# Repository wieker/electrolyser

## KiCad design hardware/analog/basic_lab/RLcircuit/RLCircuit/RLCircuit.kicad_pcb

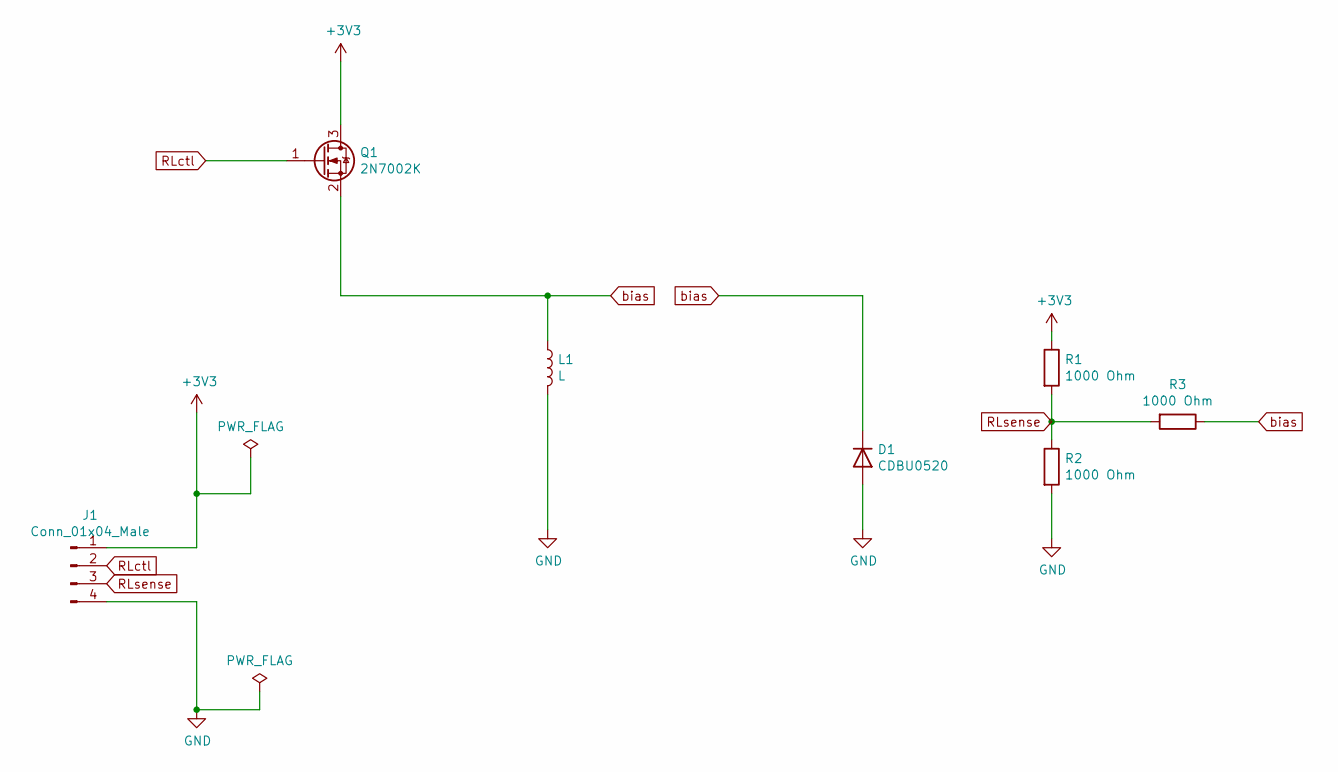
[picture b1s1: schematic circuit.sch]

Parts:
D1: CDBU0520; D_0603_1608Metric
J1: Conn_01x04_Male; PinHeader_1x04_P2.54mm_Vertical
L1: L; L_Axial_L12.0mm_D5.0mm_P5.08mm_Vertical_Fastron_MISC
Q1: 2N7002K; SOT-23
R1, R2, R3: 1000 Ohm; R_0402_1005Metric

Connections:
+3V3: J1.1, Q1.3 (D), R1.1
GND: D1.2 (A), J1.4, L1.2, R2.2
RLctl: J1.2, Q1.1 (G)
RLsense: J1.3, R1.2, R2.1, R3.2
bias: D1.1 (K), L1.1, Q1.2 (S), R3.1

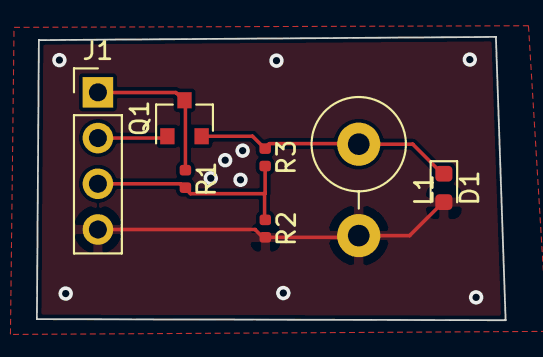
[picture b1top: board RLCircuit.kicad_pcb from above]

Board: 2 copper layers, 26.0 x 15.7 mm, 7 parts (0 on the bottom side), 5 nets.

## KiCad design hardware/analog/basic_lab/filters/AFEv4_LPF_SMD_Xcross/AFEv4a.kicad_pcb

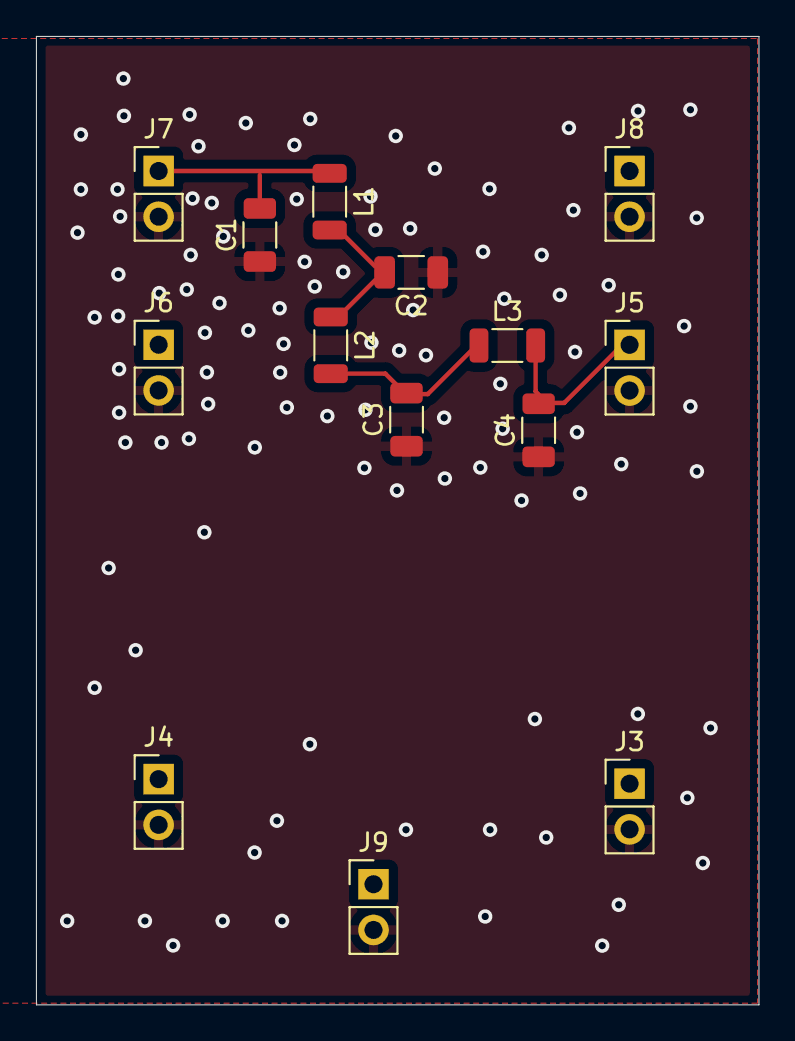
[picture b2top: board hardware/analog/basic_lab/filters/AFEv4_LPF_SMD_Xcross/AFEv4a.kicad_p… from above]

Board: 2 copper layers, 40.1 x 53.8 mm, 14 parts (0 on the bottom side), 5 nets.

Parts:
C1, C2, C3, C4: C; C_1206_3216Metric
J3, J4, J5, J6, J7, J8, J9: Connector_Generic_Conn_01x02; PinHeader_1x02_P2.54mm_Vertical
L1, L2, L3: L; L_1206_3216Metric

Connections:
GND: C1.1, C2.1, C3.1, C4.1, J3.2, J4.2, J5.2, J6.2, J7.2, J8.2, J9.2
unnamed: C2.2, L1.2, L2.1
unnamed: C3.2, L2.2, L3.1
bpf_ant: C4.2, J5.1, L3.2
bpf_lvds: C1.2, J7.1, L1.1

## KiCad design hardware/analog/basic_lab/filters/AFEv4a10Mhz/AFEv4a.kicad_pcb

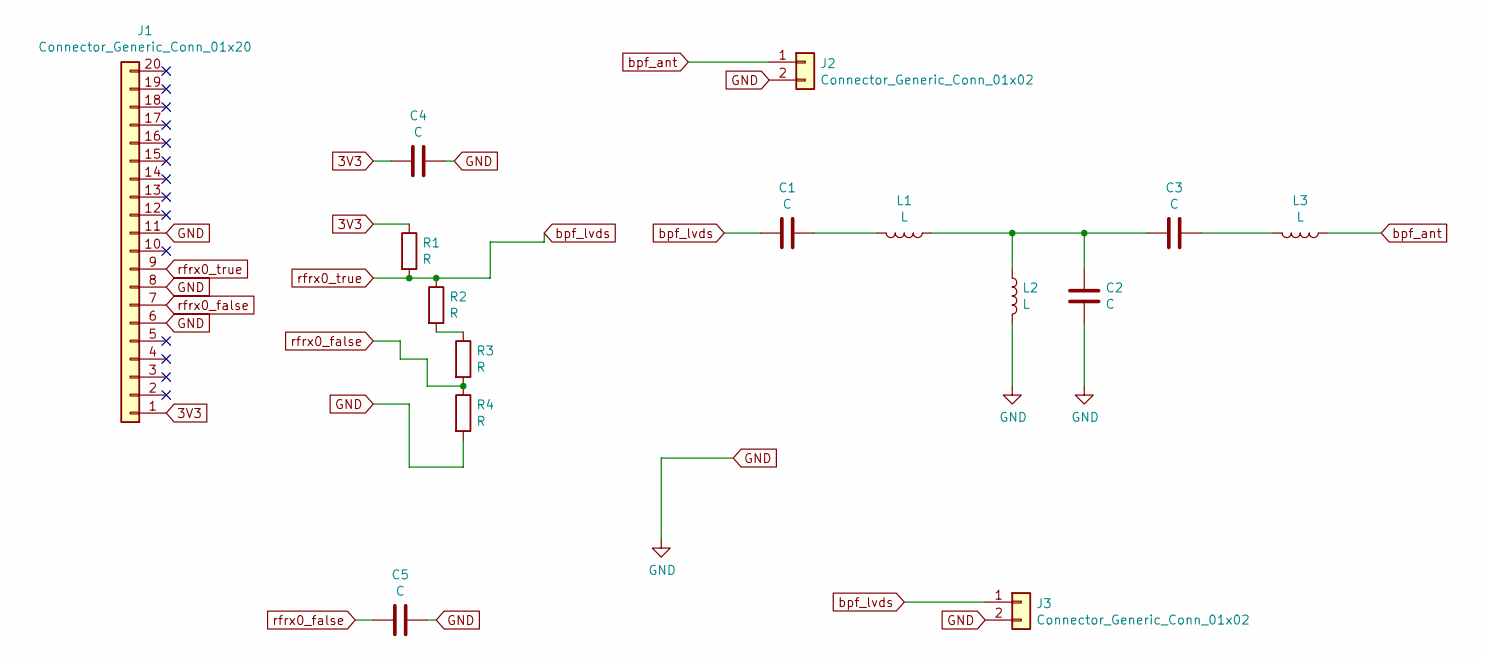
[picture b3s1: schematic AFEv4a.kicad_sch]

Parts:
C1, C2, C3: C; C_1206_3216Metric
C4, C5: C; C_Axial_L5.1mm_D3.1mm_P15.00mm_Horizontal
J1: Connector_Generic_Conn_01x20; PinHeader_1x20_P2.54mm_Vertical
J2, J3: Connector_Generic_Conn_01x02; PinHeader_1x02_P2.54mm_Vertical
L1, L2, L3: L; L_1206_3216Metric
R1, R2, R3, R4: R; R_Axial_DIN0207_L6.3mm_D2.5mm_P5.08mm_Vertical

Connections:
3V3: C4.2, J1.1, R1.1
GND: C2.2, C4.1, C5.1, J1.6, J1.8, J1.11, J2.2, J3.2, L2.2, R4.2
unnamed: C1.1, L1.2
unnamed: C2.1, C3.2, L1.1, L2.1
unnamed: C3.1, L3.2
unnamed: R2.2, R3.1
bpf_ant: J2.1, L3.1
bpf_lvds: C1.2, J1.9, J3.1, R1.2, R2.1
rfrx0_false: C5.2, J1.7, R3.2, R4.1

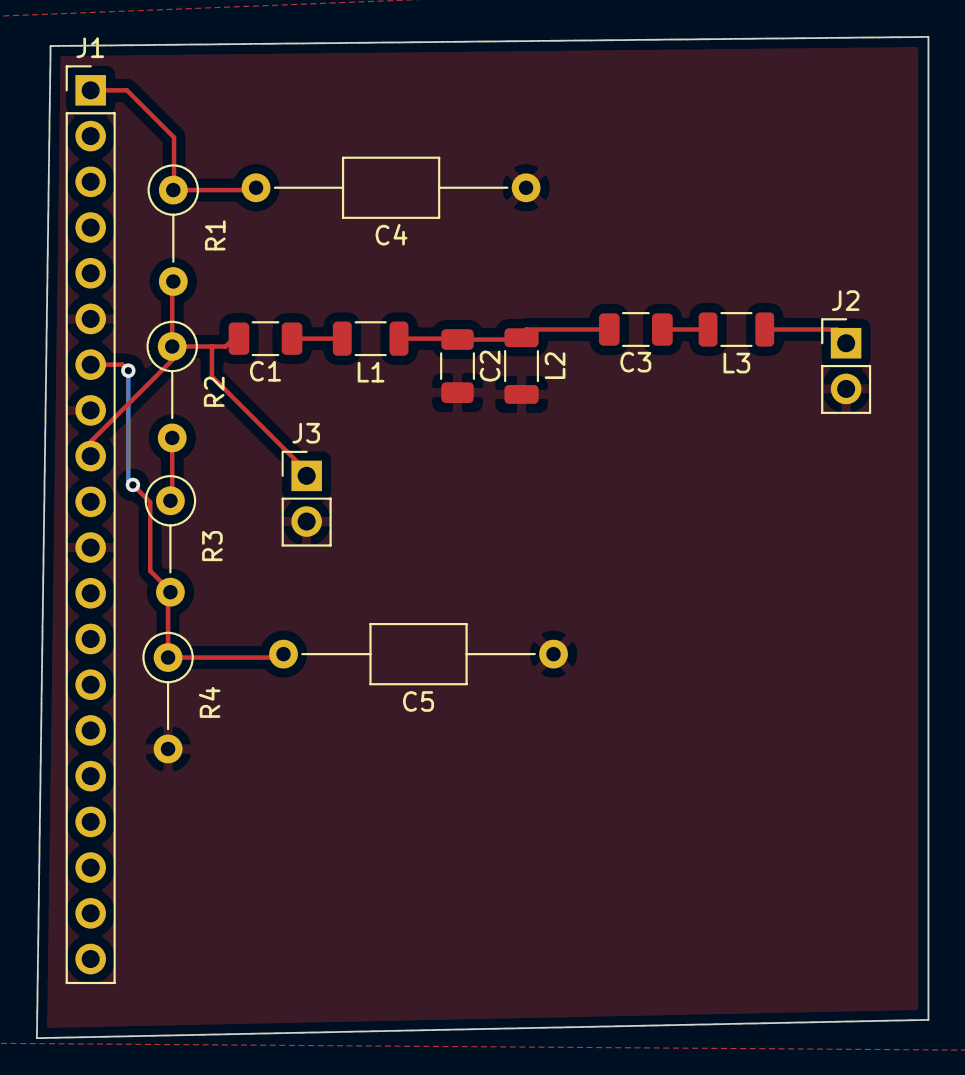
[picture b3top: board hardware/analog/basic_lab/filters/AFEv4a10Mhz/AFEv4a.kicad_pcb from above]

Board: 2 copper layers, 49.5 x 55.6 mm, 15 parts (0 on the bottom side), 9 nets.

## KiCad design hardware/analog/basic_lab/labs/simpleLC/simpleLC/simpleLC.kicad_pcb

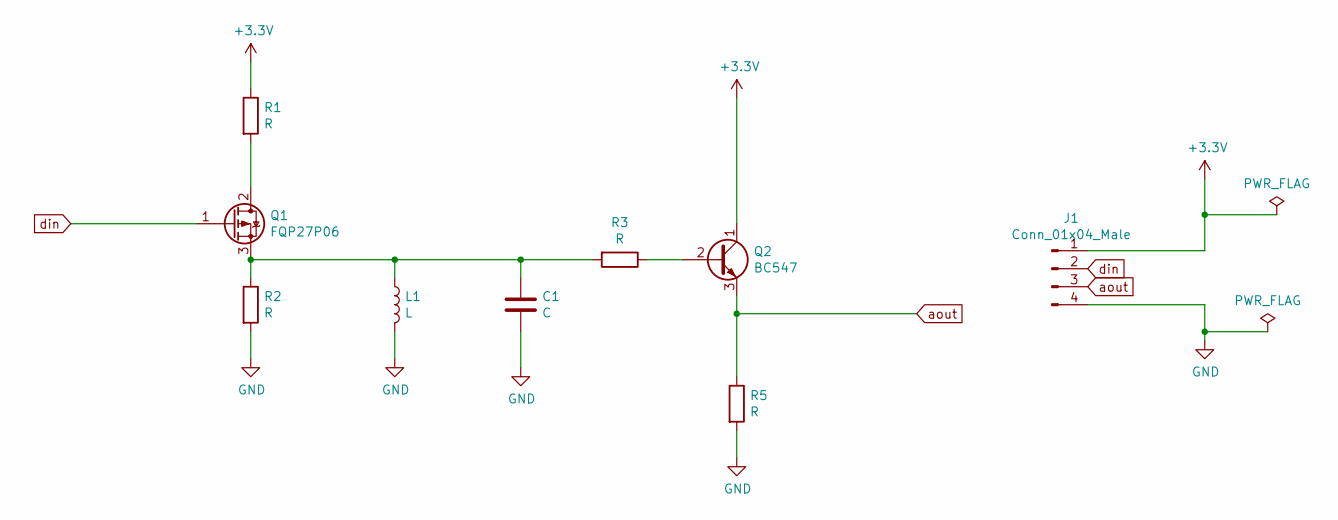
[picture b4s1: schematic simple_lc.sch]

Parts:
C1: C; C_Disc_D3.8mm_W2.6mm_P2.50mm
J1: Conn_01x04_Male; PinHeader_1x04_P2.54mm_Vertical
L1: L; L_Axial_L5.3mm_D2.2mm_P2.54mm_Vertical_Vishay_IM-1
Q1: FQP27P06; TO-220-3_Vertical
Q2: BC547; TO-92_Inline
R1, R2, R3, R5: R; R_Axial_DIN0207_L6.3mm_D2.5mm_P2.54mm_Vertical

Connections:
+3V3: J1.1, Q2.1 (C), R1.1
GND: C1.2, J1.4, L1.2, R2.2, R5.2
unnamed: C1.1, L1.1, Q1.3 (S), R2.1, R3.2
unnamed: Q1.2 (D), R1.2
unnamed: Q2.2 (B), R3.1
aout: J1.3, Q2.3 (E), R5.1
din: J1.2, Q1.1 (G)

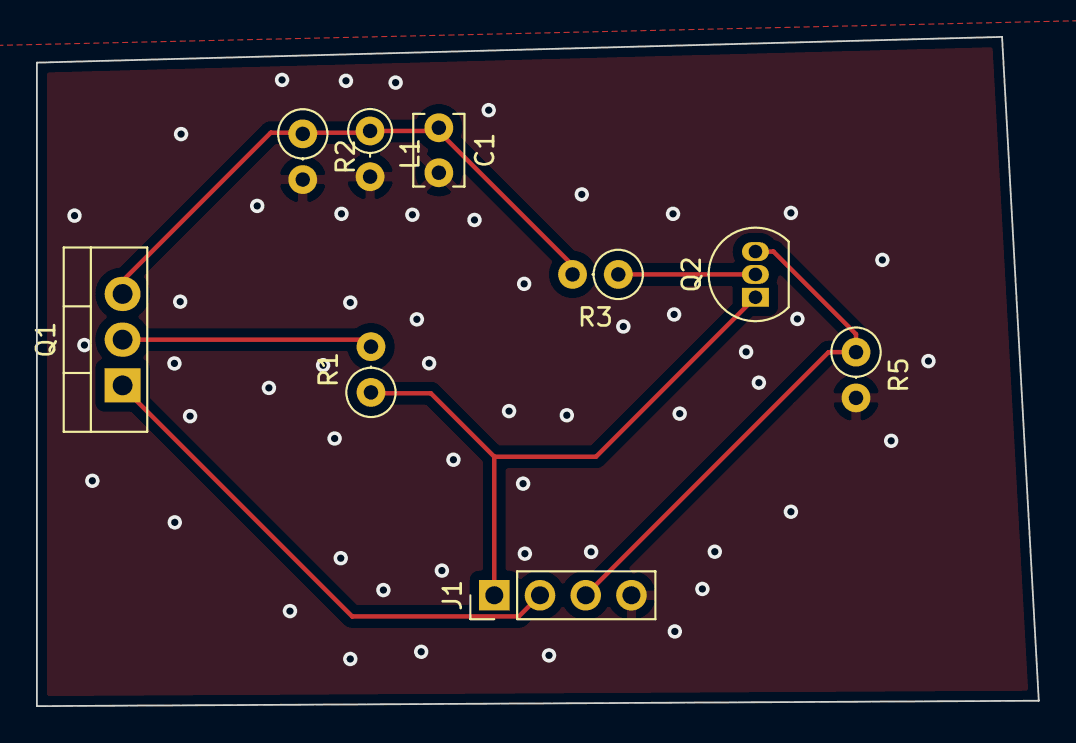
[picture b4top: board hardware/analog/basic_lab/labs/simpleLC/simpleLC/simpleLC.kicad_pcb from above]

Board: 2 copper layers, 55.7 x 37.2 mm, 9 parts (0 on the bottom side), 7 nets.

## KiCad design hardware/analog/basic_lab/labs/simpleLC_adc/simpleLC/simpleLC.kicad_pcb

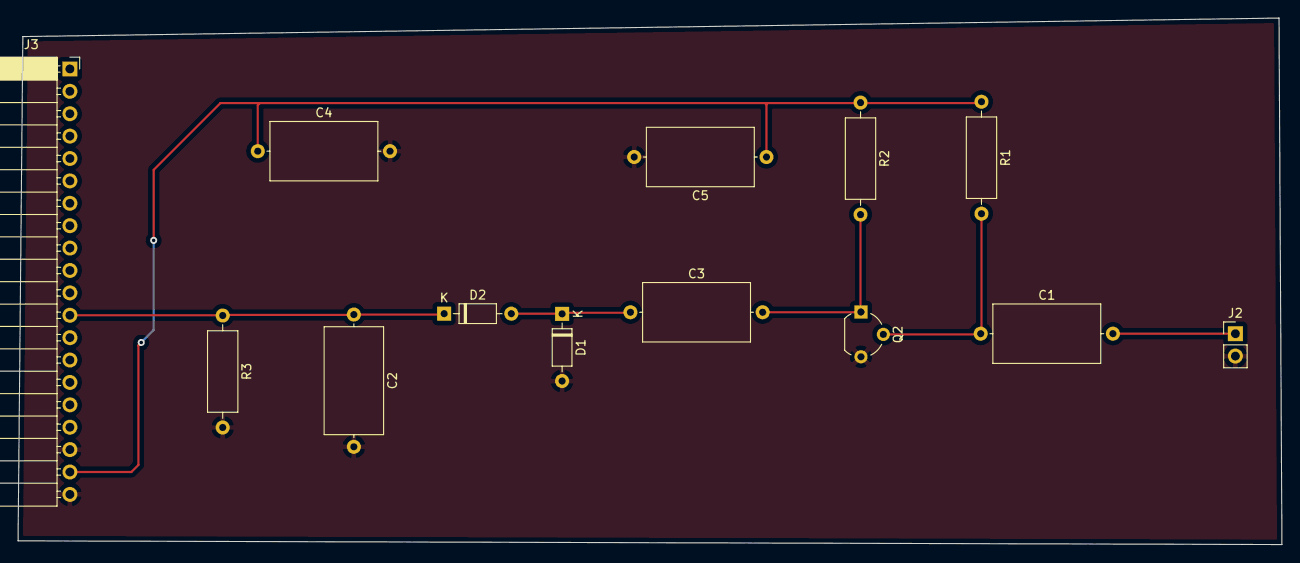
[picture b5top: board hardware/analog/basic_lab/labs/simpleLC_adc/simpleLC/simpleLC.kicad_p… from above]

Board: 2 copper layers, 143.4 x 59.7 mm, 13 parts (0 on the bottom side), 7 nets.

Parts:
C1, C2, C3, C4, C5: C; C_Axial_L12.0mm_D6.5mm_P15.00mm_Horizontal
D1, D2: 1N4148; D_DO-35_SOD27_P7.62mm_Horizontal
J2: Conn_01x02_Male; PinHeader_1x02_P2.54mm_Vertical
J3: Conn_01x20_Female; PinSocket_1x20_P2.54mm_Horizontal
Q2: BC547; TO-92_Wide
R1, R2, R3: R; R_Axial_DIN0309_L9.0mm_D3.2mm_P12.70mm_Horizontal

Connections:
+3V3: C4.1, C5.1, J3.19, R1.1, R2.1
GND: C2.2, C4.2, C5.2, D1.2, J2.2, J3.18, J3.20, Q2.3, R3.2
unnamed: C1.1, Q2.2, R1.2
unnamed: C1.2, J2.1
unnamed: C3.2, Q2.1, R2.2
adc: C2.1, D2.1, J3.12, R3.1
det: C3.1, D1.1, D2.2

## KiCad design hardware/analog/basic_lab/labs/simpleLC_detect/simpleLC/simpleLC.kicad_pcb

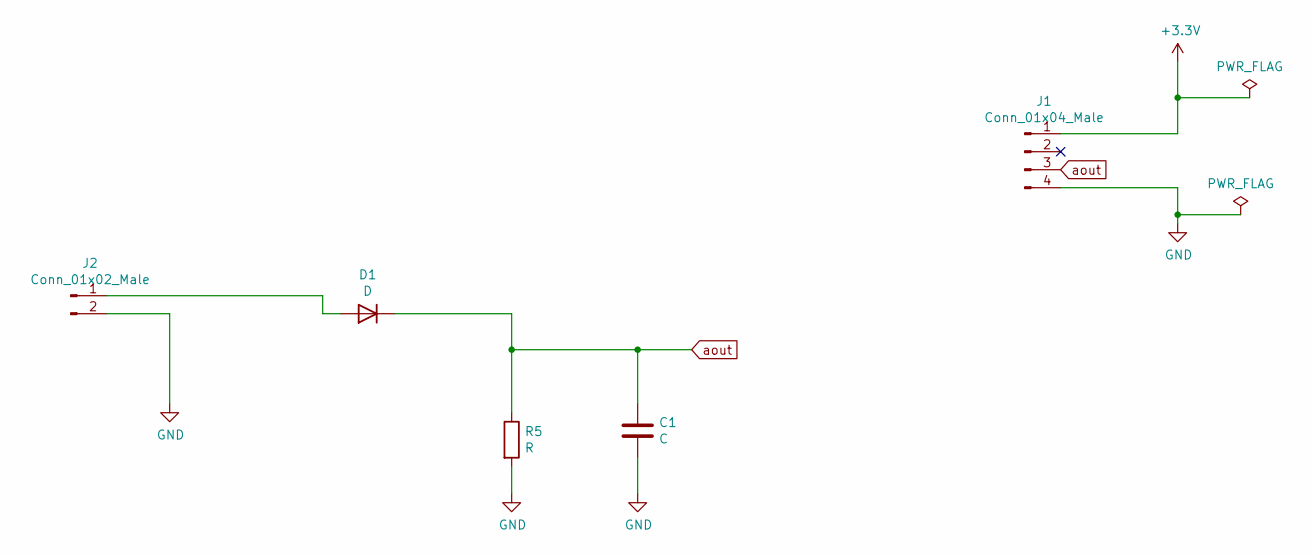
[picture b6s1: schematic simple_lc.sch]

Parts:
C1: C; C_Disc_D3.8mm_W2.6mm_P2.50mm
D1: D; D_A-405_P7.62mm_Horizontal
J1: Conn_01x04_Male; PinHeader_1x04_P2.54mm_Vertical
J2: Conn_01x02_Male; PinHeader_1x02_P2.54mm_Vertical
R5: R; R_Axial_DIN0207_L6.3mm_D2.5mm_P2.54mm_Vertical

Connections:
+3V3: J1.1
GND: C1.2, J1.4, J2.2, R5.2
unnamed: D1.2 (A), J2.1
aout: C1.1, D1.1 (K), J1.3, R5.1

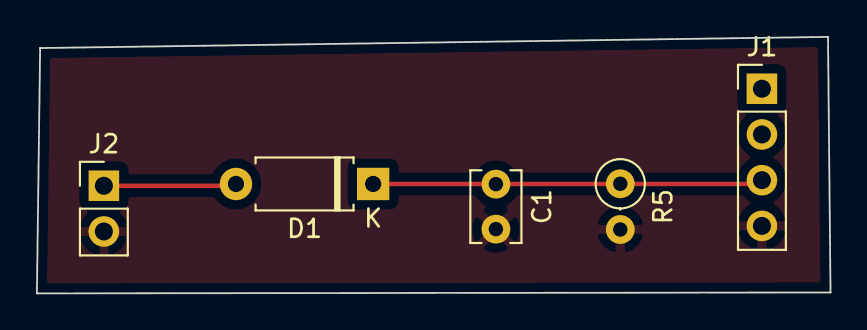
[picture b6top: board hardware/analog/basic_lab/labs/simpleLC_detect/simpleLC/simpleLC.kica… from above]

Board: 2 copper layers, 44.1 x 14.2 mm, 5 parts (0 on the bottom side), 3 nets.

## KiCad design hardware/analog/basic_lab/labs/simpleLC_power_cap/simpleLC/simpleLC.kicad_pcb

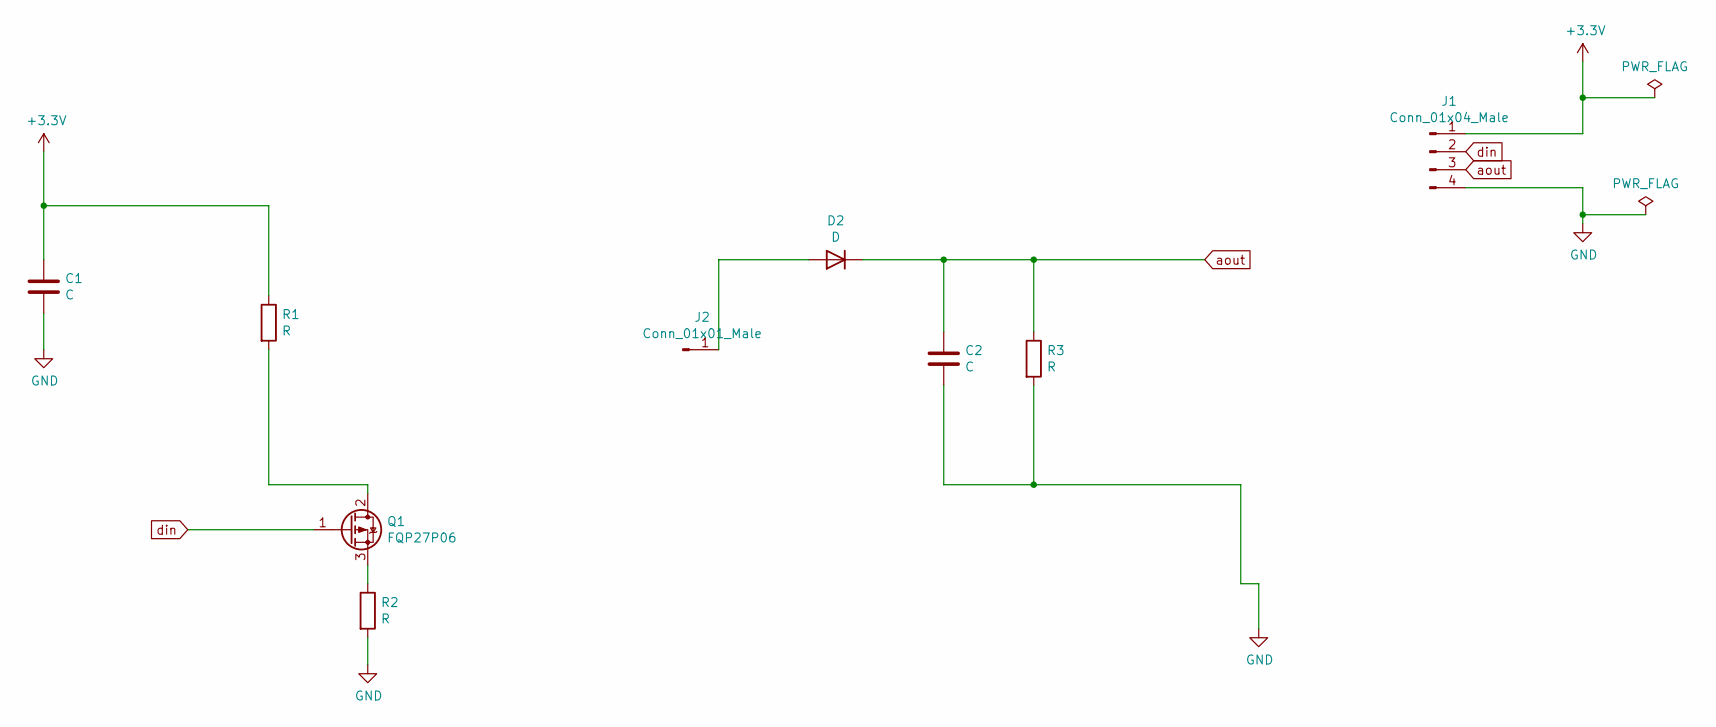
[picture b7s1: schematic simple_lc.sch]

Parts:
C1, C2: C; C_Disc_D4.3mm_W1.9mm_P5.00mm
D2: D; D_DO-15_P10.16mm_Horizontal
J1: Conn_01x04_Male; PinHeader_1x04_P2.54mm_Vertical
J2: Conn_01x01_Male; PinHeader_1x01_P2.54mm_Vertical
Q1: FQP27P06; TO-220-3_Vertical
R1, R2, R3: R; R_Axial_DIN0204_L3.6mm_D1.6mm_P5.08mm_Horizontal

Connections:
+3V3: C1.1, J1.1, R1.1
GND: C1.2, C2.2, J1.4, R2.2, R3.2
unnamed: D2.2 (A), J2.1
unnamed: Q1.2 (D), R1.2
unnamed: Q1.3 (S), R2.1
aout: C2.1, D2.1 (K), J1.3, R3.1
din: J1.2, Q1.1 (G)

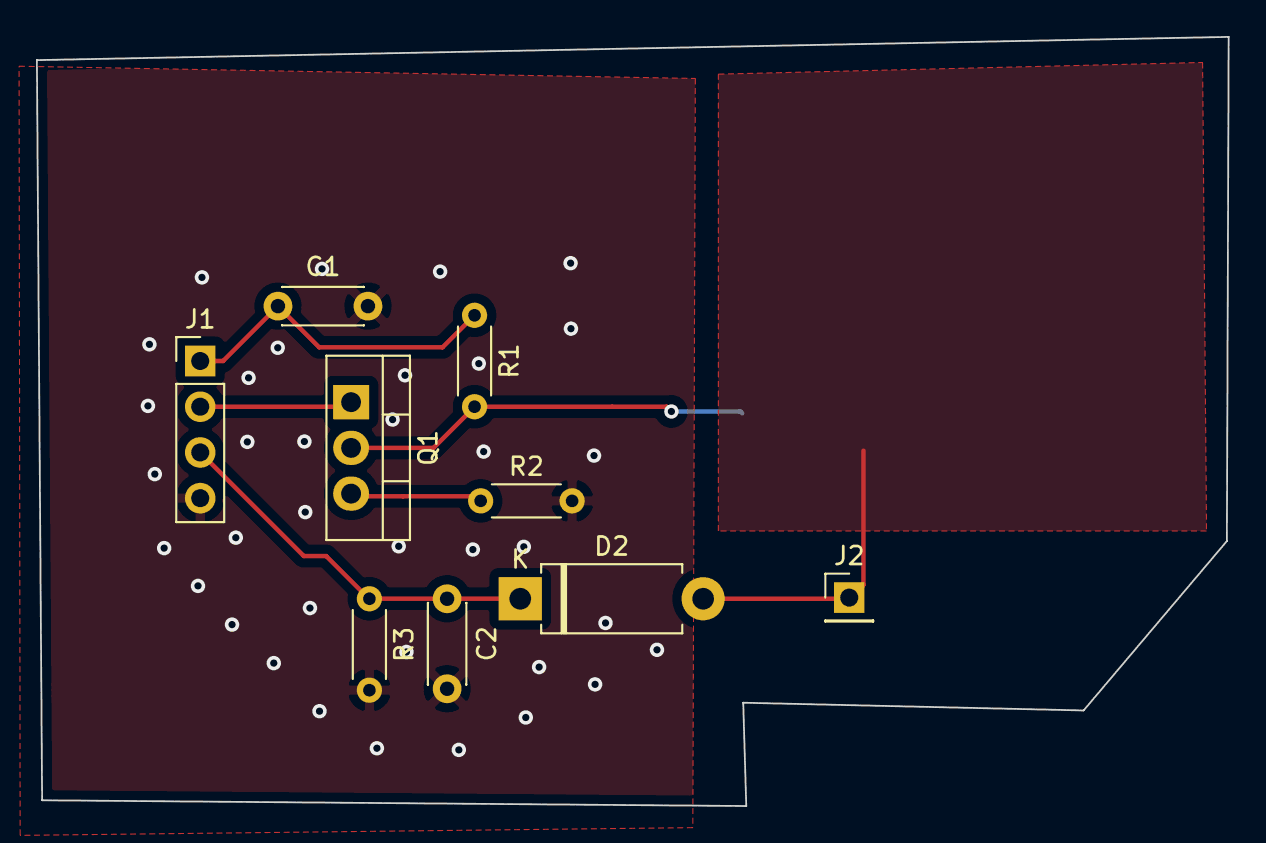
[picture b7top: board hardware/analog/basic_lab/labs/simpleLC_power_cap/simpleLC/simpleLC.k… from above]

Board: 2 copper layers, 66.2 x 42.7 mm, 9 parts (0 on the bottom side), 7 nets.
